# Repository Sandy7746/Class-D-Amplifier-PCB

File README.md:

# Class-D-Amplifier-PCB
High-efficiency Class-D audio amplifier PCB designed in KiCad using PWM control and LC filtering for clean amplified output.
# Class-D Amplifier PCB Design 🎛️

## 📘 Project Overview
This repository contains the **KiCad schematic and PCB design** for a **Class-D Audio Amplifier**, built using simple and easily available components.  
The goal is to design a **high-efficiency amplifier** that uses **pulse-width modulation (PWM)** to amplify an audio signal while minimizing power loss.

---

## ⚙️ Working Principle
A **Class-D amplifier** works by converting the input analog audio signal into a high-frequency **PWM signal**.  
Instead of linearly amplifying the input like Class A or AB amplifiers, it uses **switching elements (MOSFETs)** that operate in ON/OFF states, drastically improving efficiency.

Here’s the functional breakdown of how this circuit works:

1. 🎵 **Audio Input Stage**  
   - The input analog signal is given to a **comparator (LM311)**.  
   - The comparator compares the audio signal with a **high-frequency triangular waveform** to generate a **PWM signal**.  
   - The width of each pulse corresponds to the amplitude of the input signal.

2. ⚡ **Driver Stage**  
   - The PWM signal is fed to the **IR2153 driver IC**, which is used to drive the **MOSFETs** efficiently.  
   - It provides **high-side and low-side gate control**, ensuring proper switching timing.

3. 🔁 **Switching Stage**  
   - **IRFP4668PBF MOSFETs** are used as the main switching devices.  
   - They switch ON and OFF at high frequency according to the PWM signal, creating a high-power modulated waveform.

4. 🔊 **Output Filter Stage (LC Filter)**  
   - The high-frequency PWM output passes through a **low-pass LC filter (35µH inductor + capacitor)**.  
   - This filter removes the switching frequency, reconstructing the original amplified analog signal.  
   - The output is a **clean, amplified audio signal** suitable for driving a speaker.

5. 🔋 **Power Supply and Protection**  
   - **Zener diodes (1N47xxA series)** provide voltage regulation and protect sensitive ICs.  
   - **Decoupling capacitors (0.1µF)** reduce switching noise and improve stability.

---

## 🧠 Design Highlights
- ✅ **High Efficiency:** Uses switching operation for minimal heat dissipation.  
- ✅ **Compact Layout:** Two-layer PCB with optimized routing and short return paths.  
- ✅ **Noise Control:** Proper placement of decoupling capacitors and ground planes.  
- ✅ **Easy Assembly:** Clearly labeled components and silkscreen markings.  

---

## 🛠️ Design Environment
- **Software:** KiCad v9.0  
- **Layers:** 2 (Top & Bottom)  
- **DRC Check:** Passed successfully ✅  
- **3D View:** Verified component placement and clearances

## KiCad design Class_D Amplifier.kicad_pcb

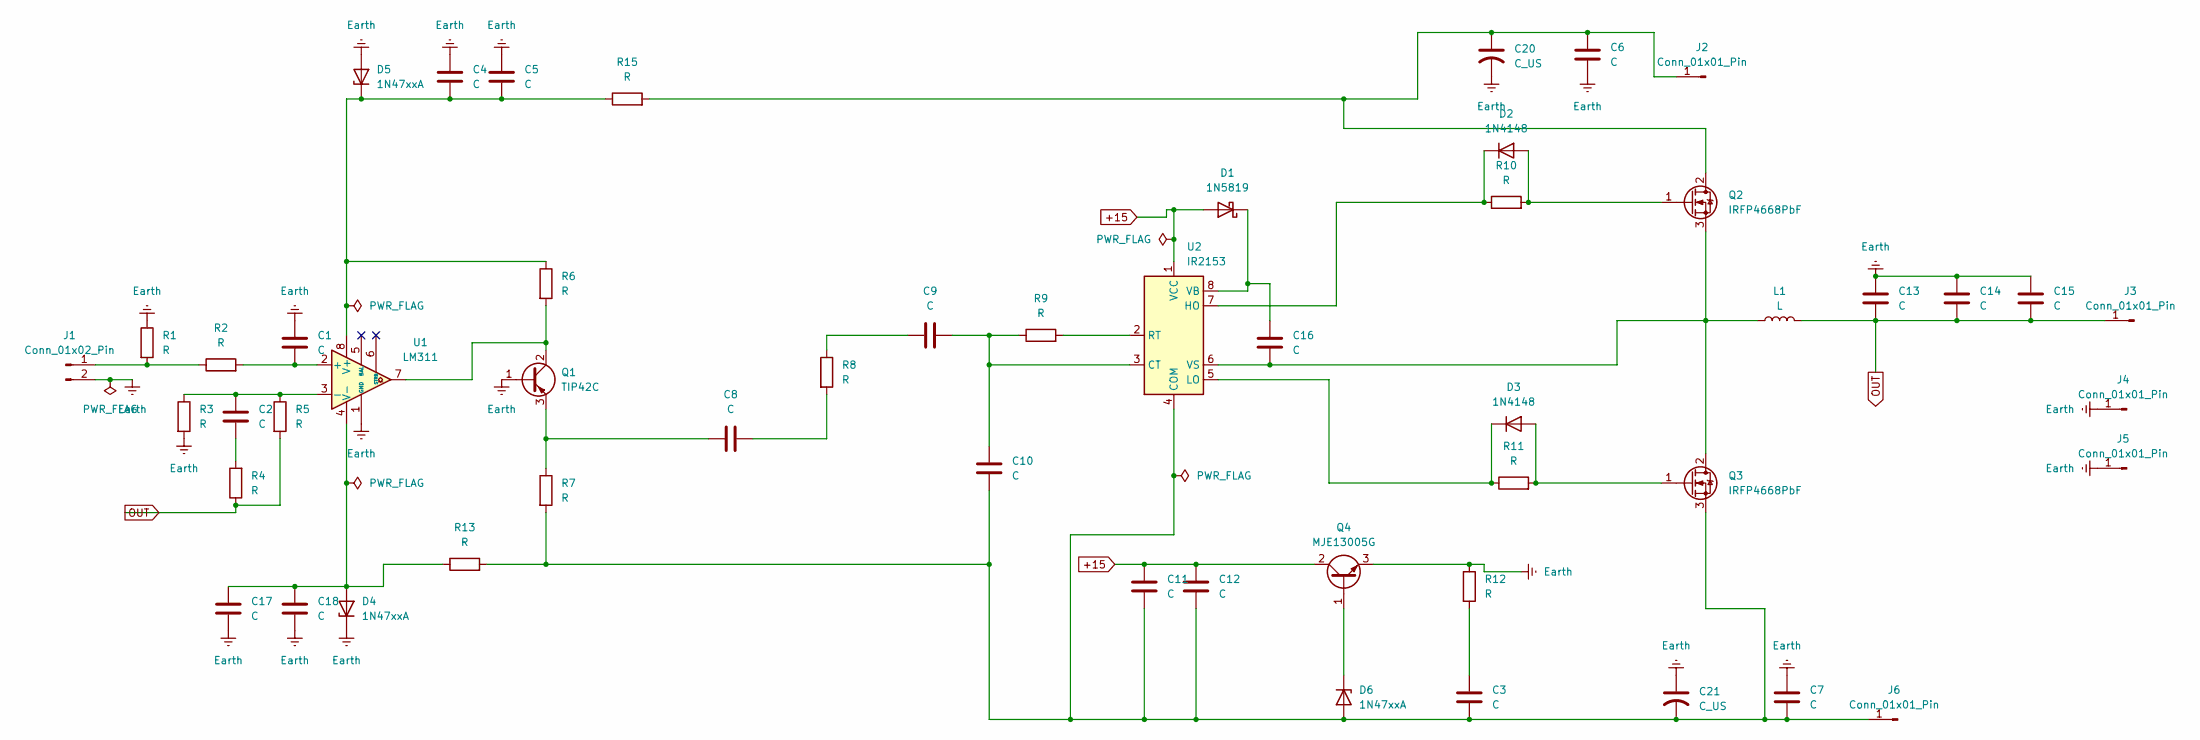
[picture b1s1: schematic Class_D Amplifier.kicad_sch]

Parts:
C1, C2, C3, C4, C5, C6, C7, C8, C9, C10, C11, C12, C13, C14, C15, C16, C17, C18: C; CP_Radial_D8.0mm_P3.50mm
C20, C21: C_US; CP_Radial_D8.0mm_P3.50mm
D1: 1N5819; D_DO-41_SOD81_P10.16mm_Horizontal
D2, D3: 1N4148; D_DO-35_SOD27_P7.62mm_Horizontal
D4, D5, D6: 1N47xxA; D_DO-41_SOD81_P10.16mm_Horizontal
J1: Conn_01x02_Pin; Pin_D1.0mm_L10.0mm
J2, J3, J4, J5, J6: Conn_01x01_Pin; Pin_D1.0mm_L10.0mm
L1: L; L_Radial_D6.0mm_P4.00mm
Q1: TIP42C; TO-220-3_Vertical
Q2, Q3: IRFP4668PbF; TO-247-3_Vertical
Q4: MJE13005G; TO-220-3_Vertical
R1, R2, R3, R4, R5, R6, R7, R8, R9, R10, R11, R12, R13, R15: R; R_Box_L8.4mm_W2.5mm_P5.08mm
U1: LM311; DIP-8_W7.62mm
U2: IR2153; DIP-8_W7.62mm

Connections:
+15: C11.1, C12.1, D1.2 (A), Q4.2 (C), U2.1 (VCC)
Earth: C1.1, C4.1, C5.1, C6.2, C7.1, C13.1, C14.1, C15.1, C17.2, C18.2, C20.2, C21.1, D4.1 (K), D5.2 (A), J1.2, J4.1, J5.1, Q1.1 (B), Q4.3 (E), R1.1, R3.2, R12.1, U1.1 (GND)
unnamed: C2.2, R4.2
unnamed: C3.1, R12.2
unnamed: C8.2, R8.2
unnamed: C9.1, R8.1
unnamed: C16.1, D1.1 (K), U2.8 (VB)
unnamed: D2.2 (A), Q2.1 (G), R10.2
unnamed: D2.1 (K), R10.1, U2.7 (HO)
unnamed: D3.2 (A), Q3.1 (G), R11.2
unnamed: D3.1 (K), R11.1, U2.5 (LO)
unnamed: C17.1, C18.1, D4.2 (A), R13.1, U1.4 (V-)
unnamed: C4.2, C5.2, D5.1 (K), R6.1, R15.1, U1.8 (V+)
unnamed: C3.2, C7.2, C10.2, C11.2, C12.2, C21.2, D6.2 (A), J6.1, Q3.3 (S), R7.2, R13.2, U2.4 (COM)
unnamed: D6.1 (K), Q4.1 (B)
unnamed: J1.1, R1.2, R2.1
unnamed: C6.1, C20.1, J2.1, Q2.2 (D), R15.2
unnamed: Q1.2 (C), R6.2, U1.7
unnamed: C8.1, Q1.3 (E), R7.1
unnamed: C16.2, L1.1, Q2.3 (S), Q3.2 (D), U2.6 (VS)
unnamed: C1.2, R2.2, U1.2 (+)
unnamed: C2.1, R3.1, R5.1, U1.3 (-)
unnamed: C9.2, C10.1, R9.1, U2.3 (CT)
unnamed: R9.2, U2.2 (RT)
OUT: C13.2, C14.2, C15.2, J3.1, L1.2, R4.1, R5.2

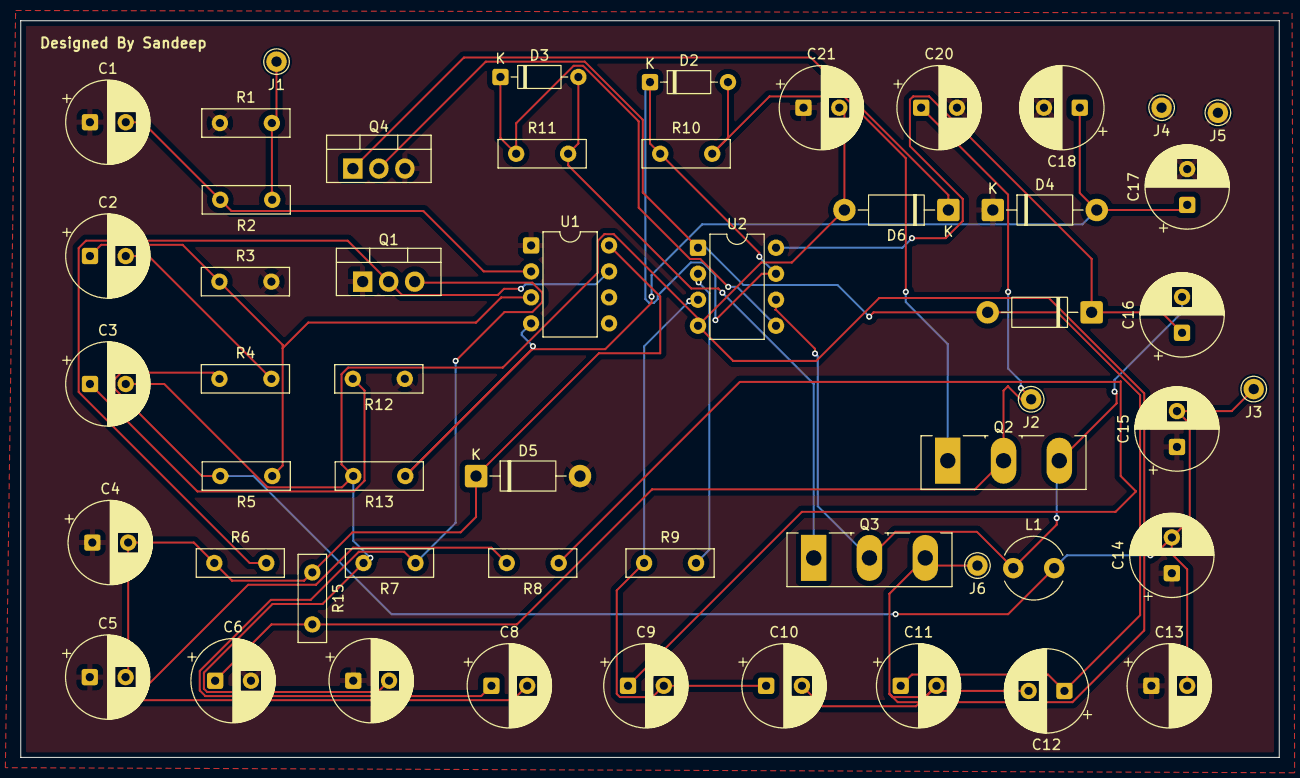
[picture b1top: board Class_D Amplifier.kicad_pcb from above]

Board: 2 copper layers, 123.0 x 72.0 mm, 53 parts (0 on the bottom side), 25 nets.
